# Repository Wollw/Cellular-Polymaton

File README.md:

#Cellular Polymaton#
##About##
This implements a generalized cellular automaton framework for creating
automaton using unique geometry.  I created this to allow me to make sculptures using light to represent cell state using shapes other than a
simple square grid.  This required being able to explicitly say which
cells are neighbors to each other.  The project is available under the MIT
License.

##Configuration##
Make a duplicate of one of the projects in the "projects" directory,
change the Makefile's CONFIG\_H  variable to point to the correct
file, and edit the config.h file to your liking.

###Required###
	#define	CFG_CELL_COUNT	<size_t>
The number of cells in the automaton.

	#define CFG_MOST_NEIGHBORS	<size_t>
The number of neighbor cells the cell with the most neighbors has.

	struct rules cfg_rules
The members 'live' and 'dead' define the rules for cells that are
alive and dead.  For example `{ 0b00001100, 0b00001000 }`
defines rules for Conway's Game of Life.  The first bit field
has bits 2 and 3 set, meaning cells with 2 or 3 living neighbors
will stay alive (as the first rule set is for currently living
cells).  The second bit field has only bit 3 set, meaning cells
with three living neighbors will be born (as the second rule set is
for cells that are currently dead).

	struct cells cfg_cells
This has two members, 'neighbors' and 'initial\_state'.  'neighbors'
defines the cells that are considered neighbors to each cell and
'initial\_state' defines the initial state of the cell.  Cell's are
identified by the position in the cfg\_cells[] array and neighbor
relationships are defined in a bit field such that a bit field of 
0b1100 means a cell is neighbors with the cells at index 2 and 3 (as bits
2 and 3 are set).  'initial\_state' is either 'DEAD' or 'LIVE' but these
are truly just macros for false and true respectively so boolean values
can be used as well.  As an example here is a simple cfg\_cells array
defining a two cell automaton where the first cell starts out alive
the second starts dead and they are both neighbors to eachother:
	`{
		{ 0b10, LIVE },
		{ 0b01, DEAD }
	}`

###Optional###
	#define	CFG_WAIT_COUNT <int>
The number of interrupts to left occur before updating the world's state.
Defaults to 1.

	#define CFG_ENABLE_USART
If this is defined the automaton will output cell data over serial.

	#define	CFG_USART_BAUDRATE	<uint64_t>
This defines the baudrate of the serial port.

	#define	CFG_USART_SET_BIT_MSG	<char[]>
	#define	CFG_USART_CLR_BIT_MSG	<char[]>
The string to use when outputting the bit states over serial.  These are
"1" and "0" by default.

	#define CFG_ENABLE_SHIFT
If defined the state will be shifted out to a shift register (like the
74HC595) using the definitions below.

	#define CFG_SHIFT_REGISTER_PIN_COUNT	<int>
The total number of pins between all the shift registers including unused
pins.  If you have three 74HC595 shift registers then this number will be
24 because 8 * 3 is 24.

	#define	CFG_SHIFT_DDR	<DDRn>
	#define	CFG_SHIFT_PORT	<PORTn>
	#define	CFG_RCLK		<PINn>
	#define	CFG_SER			<PINn>
	#define	CFG_SRCLK		<PINn>
The ports and pins used for controlling the shift registers. If you are
using `PB0`, `PB1`, and `PB2` to respectively control the `RCLK`, `SER`,
and `SRCLK` pins of the shift registers then you would define them as
follows:

	#define	CFG_SHIFT_DDR	DDRB
	#define	CFG_SHIFT_PORT	PORTB
	#define	CFG_RCLK		PIN0
	#define	CFG_SER			PIN1
	#define	CFG_SRCLK		PIN2

##Compilation##

Build:
	$ make -f projects/PROJECT_DIR/Makefile

Flash:
	$ make -f projects/PROJECT_DIR/Makefile program

Clean:
	$ make -f projects/PROJECT_DIR/Makefile clean

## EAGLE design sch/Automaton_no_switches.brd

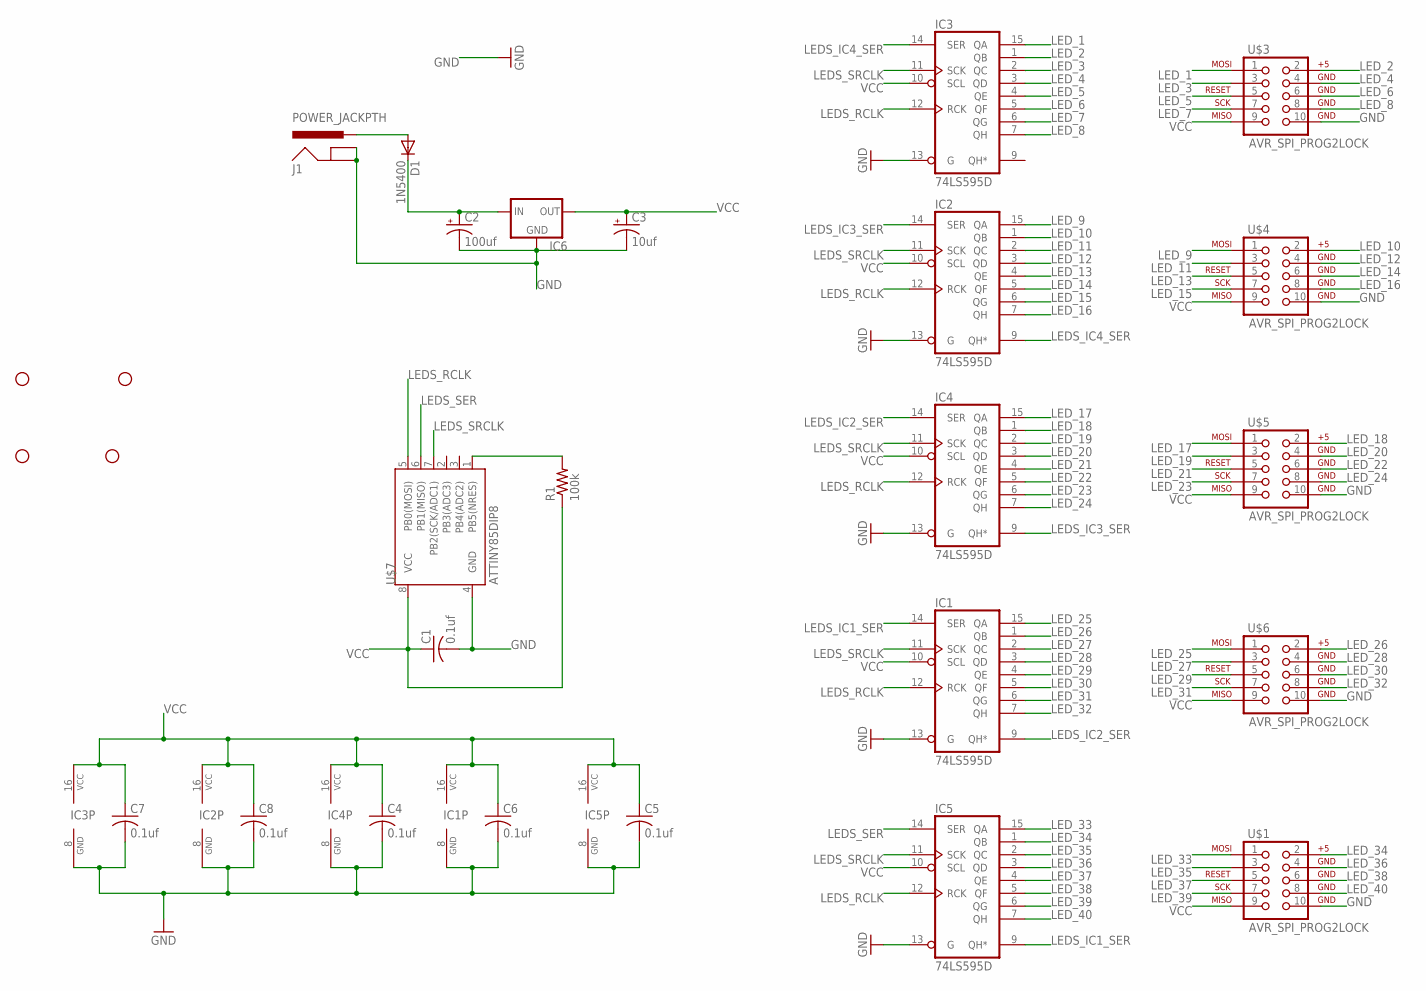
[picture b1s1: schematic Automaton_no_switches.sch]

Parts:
C1, C4, C5, C6, C7, C8: 0.1uf; C1206
C2: 100uf; E5-10,5
C3: 10uf; E2-5
D1: 1N5400; DO201-15
IC1, IC2, IC3, IC4, IC5: 74LS595D; SO16
IC6: V_REG_78XXSINK; TO220-IGO
J1: POWER_JACKPTH; POWER_JACK_PTH
JP1, JP2, JP3, JP4: STAND-OFF
R1: 100k; M1206
U$1, U$3, U$4, U$5, U$6: AVR_SPI_PROG2LOCK; 2X5-SHROUDED_LOCK
U$7: ATTINY85DIP8; DIP08

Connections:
GND: C1.2, C2.-, C3.-, C4.2, C5.2, C6.2, C7.2, C8.2, IC1.8 (GND), IC1.13 (G), IC2.8 (GND), IC2.13 (G), IC3.8 (GND), IC3.13 (G), IC4.8 (GND), IC4.13 (G), IC5.8 (GND), IC5.13 (G), IC6.GND, J1.GND, J1.GNDBREAK, U$1.10, U$3.10, U$4.10, U$5.10, U$6.10, U$7.4 (GND)
LEDS_IC1_SER: IC1.14 (SER), IC5.9 (QH*)
LEDS_IC2_SER: IC1.9 (QH*), IC4.14 (SER)
LEDS_IC3_SER: IC2.14 (SER), IC4.9 (QH*)
LEDS_IC4_SER: IC2.9 (QH*), IC3.14 (SER)
LEDS_RCLK: IC1.12 (RCK), IC2.12 (RCK), IC3.12 (RCK), IC4.12 (RCK), IC5.12 (RCK), U$7.5 (PB0(MOSI))
LEDS_SER: IC5.14 (SER), U$7.6 (PB1(MISO))
LEDS_SRCLK: IC1.11 (SCK), IC2.11 (SCK), IC3.11 (SCK), IC4.11 (SCK), IC5.11 (SCK), U$7.7 (PB2(SCK/ADC1))
LED_1: IC3.15 (QA), U$3.1
LED_2: IC3.1 (QB), U$3.2
LED_3: IC3.2 (QC), U$3.3
LED_4: IC3.3 (QD), U$3.4
LED_5: IC3.4 (QE), U$3.5
LED_6: IC3.5 (QF), U$3.6
LED_7: IC3.6 (QG), U$3.7
LED_8: IC3.7 (QH), U$3.8
LED_9: IC2.15 (QA), U$4.1
LED_10: IC2.1 (QB), U$4.2
LED_11: IC2.2 (QC), U$4.3
LED_12: IC2.3 (QD), U$4.4
LED_13: IC2.4 (QE), U$4.5
LED_14: IC2.5 (QF), U$4.6
LED_15: IC2.6 (QG), U$4.7
LED_16: IC2.7 (QH), U$4.8
LED_17: IC4.15 (QA), U$5.1
LED_18: IC4.1 (QB), U$5.2
LED_19: IC4.2 (QC), U$5.3
LED_20: IC4.3 (QD), U$5.4
LED_21: IC4.4 (QE), U$5.5
LED_22: IC4.5 (QF), U$5.6
LED_23: IC4.6 (QG), U$5.7
LED_24: IC4.7 (QH), U$5.8
LED_25: IC1.15 (QA), U$6.1
LED_26: IC1.1 (QB), U$6.2
LED_27: IC1.2 (QC), U$6.3
LED_28: IC1.3 (QD), U$6.4
LED_29: IC1.4 (QE), U$6.5
LED_30: IC1.5 (QF), U$6.6
LED_31: IC1.6 (QG), U$6.7
LED_32: IC1.7 (QH), U$6.8
LED_33: IC5.15 (QA), U$1.1
LED_34: IC5.1 (QB), U$1.2
LED_35: IC5.2 (QC), U$1.3
LED_36: IC5.3 (QD), U$1.4
LED_37: IC5.4 (QE), U$1.5
LED_38: IC5.5 (QF), U$1.6
LED_39: IC5.6 (QG), U$1.7
LED_40: IC5.7 (QH), U$1.8
unnamed: C2.+, D1.C, IC6.IN
unnamed: R1.2, U$7.1 (PB5(NRES))
unnamed: D1.A, J1.PWR
VCC: C1.1, C3.+, C4.1, C5.1, C6.1, C7.1, C8.1, IC1.10 (SCL), IC1.16 (VCC), IC2.10 (SCL), IC2.16 (VCC), IC3.10 (SCL), IC3.16 (VCC), IC4.10 (SCL), IC4.16 (VCC), IC5.10 (SCL), IC5.16 (VCC), IC6.OUT, R1.1, U$1.9, U$3.9, U$4.9, U$5.9, U$6.9, U$7.8 (VCC)

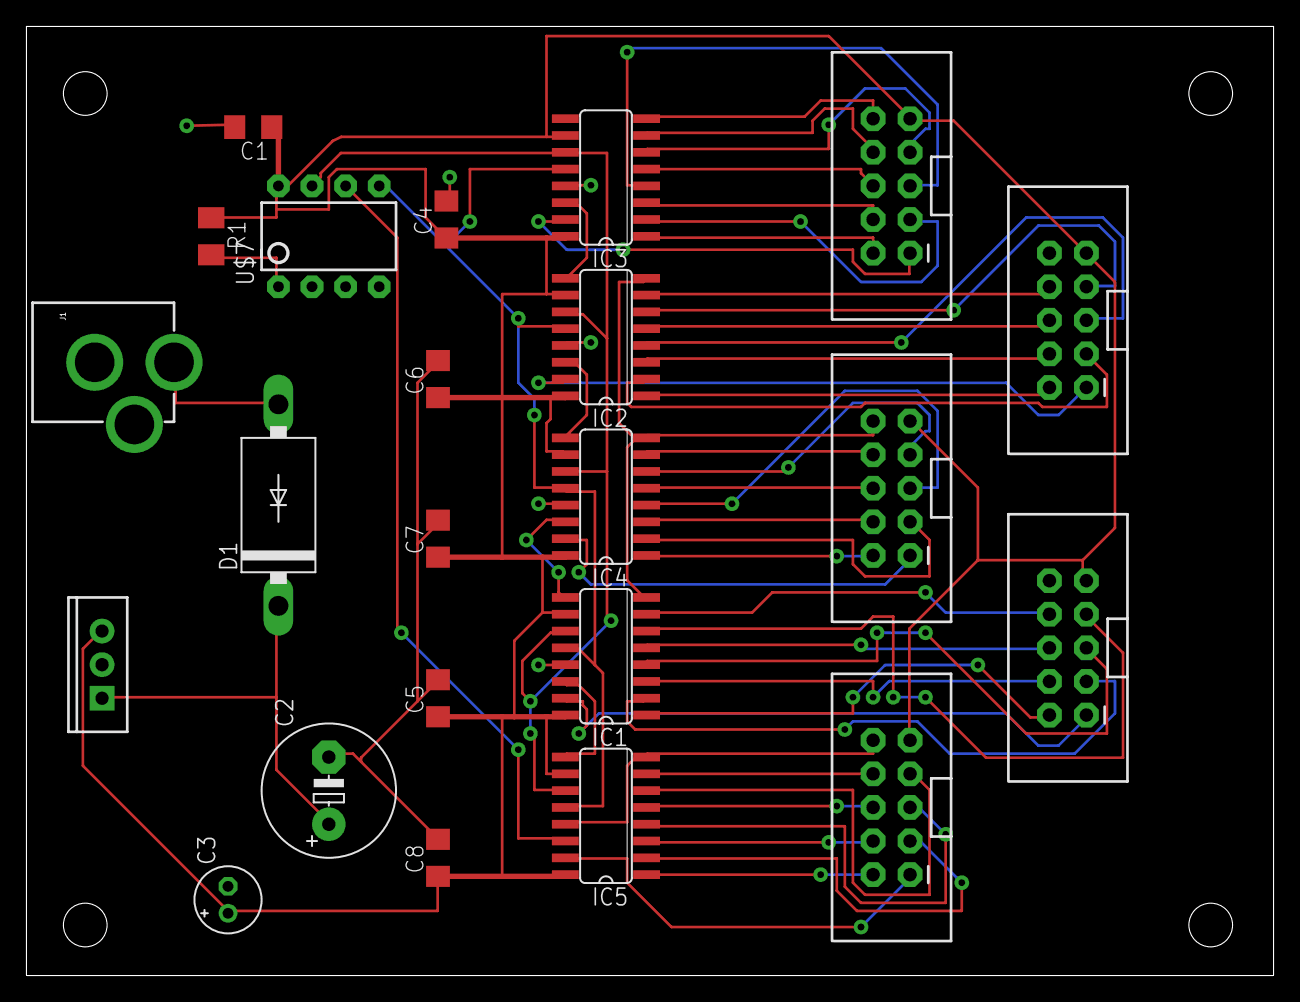
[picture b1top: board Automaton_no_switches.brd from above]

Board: 2 copper layers, 94.3 x 71.8 mm, 27 parts (0 on the bottom side), 52 nets.

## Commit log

2012-03-02 started rewrite of Automaton AVR. The logic is written and serial data can be output. Output to shift registers still needs to be reimplemented.
2012-03-02 removed old configs
2012-03-02 added warning to README
2012-03-02 changed live/dead defines to uppercase so rules can use the lower case words
2012-03-02 missed a uint64_t that needs to be changed to bits_t. corrected now.
2012-03-02 added some more comments, tweaked a few things
2012-03-02 fixed update_flag's initial value
2012-03-03 added comments to config.h, moved some constant definitions to a defines.h file
2012-03-03 removed some unneeded typedefs and moved the cell_state_t typedef to defines.h
2012-03-03 Added shift out support for parts like 74HC595.
2012-03-03 Changed pin configuration for shift registers to use a single number for pin count.
2012-03-03 updated TODO list
2012-03-03 fixed an error in the README.md file
2012-03-03 fixed pint count error in config.h
2012-03-03 added some info about the timer to the readme and some code style changes
2012-03-03 made the string displayed for set and cleared bits definable in config.h. also added more data to the initial transmission of cell data on startup.
2012-03-03 added some config files
2012-03-03 using ansi codes for output
2012-03-03 moved interrupt code to it's own file. added some preprocessor stuff to configure interrupts for the ATtiny85 and the ATtiny328P based on which is being compiled for. added a configuration define for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
2012-03-04 removed a commented line of old code from shift.c
2012-03-05 Deleted extra line in main.c comment
2012-03-06 made automaton parameters to local automaton helper functions const
2012-03-06 created flags_t type for holding status information. moved update flag to a variable of said type
2012-03-06 made rules and cell data const. started tracking some KiCAD files.
2012-03-07 switched to avrisp2 programmer
2012-03-07 recreated board file and made config.g for Automaton 0x01
2012-03-07 fixed automaton 0x01 target name
2012-03-07 tweaked config.h for automaton 0x01
2012-03-17 changed avrsize args to use the more readable format
2012-03-21 moved flags code to own files
2012-04-04 changed all foo_t types to foo_type to avoid reserved identifiers. changed examples to projects and made using those makefiles copy the right config.h to the src file so you can just make with one of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
2012-04-04 fixed error in README where path was wrong for projects
2012-04-14 moved if statement into atomic block
2012-05-01 added todo list item for changing to switching regulator
2012-05-01 added NOTES file with url for a potential power supply
2012-05-02 added firmware for Automaton 0x01
2012-05-16 changed Automaton 0x01 config a bit for the final sculpture. sculpture Automaton 0x01 is now working.
2012-05-24 added site
2012-05-24 fixed batchpcb url
2012-05-26 removed blank line
2012-06-16 removed underscore prefixed identifiers
2013-09-29 Changed video urls.
2013-09-29 Changed video size/
2014-06-05 removed

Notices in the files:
parts and their libraries:
SparkFun-PowerIC: Licensing: CC v3.0 Share-Alike You are welcome to use this library for commercial purposes.
